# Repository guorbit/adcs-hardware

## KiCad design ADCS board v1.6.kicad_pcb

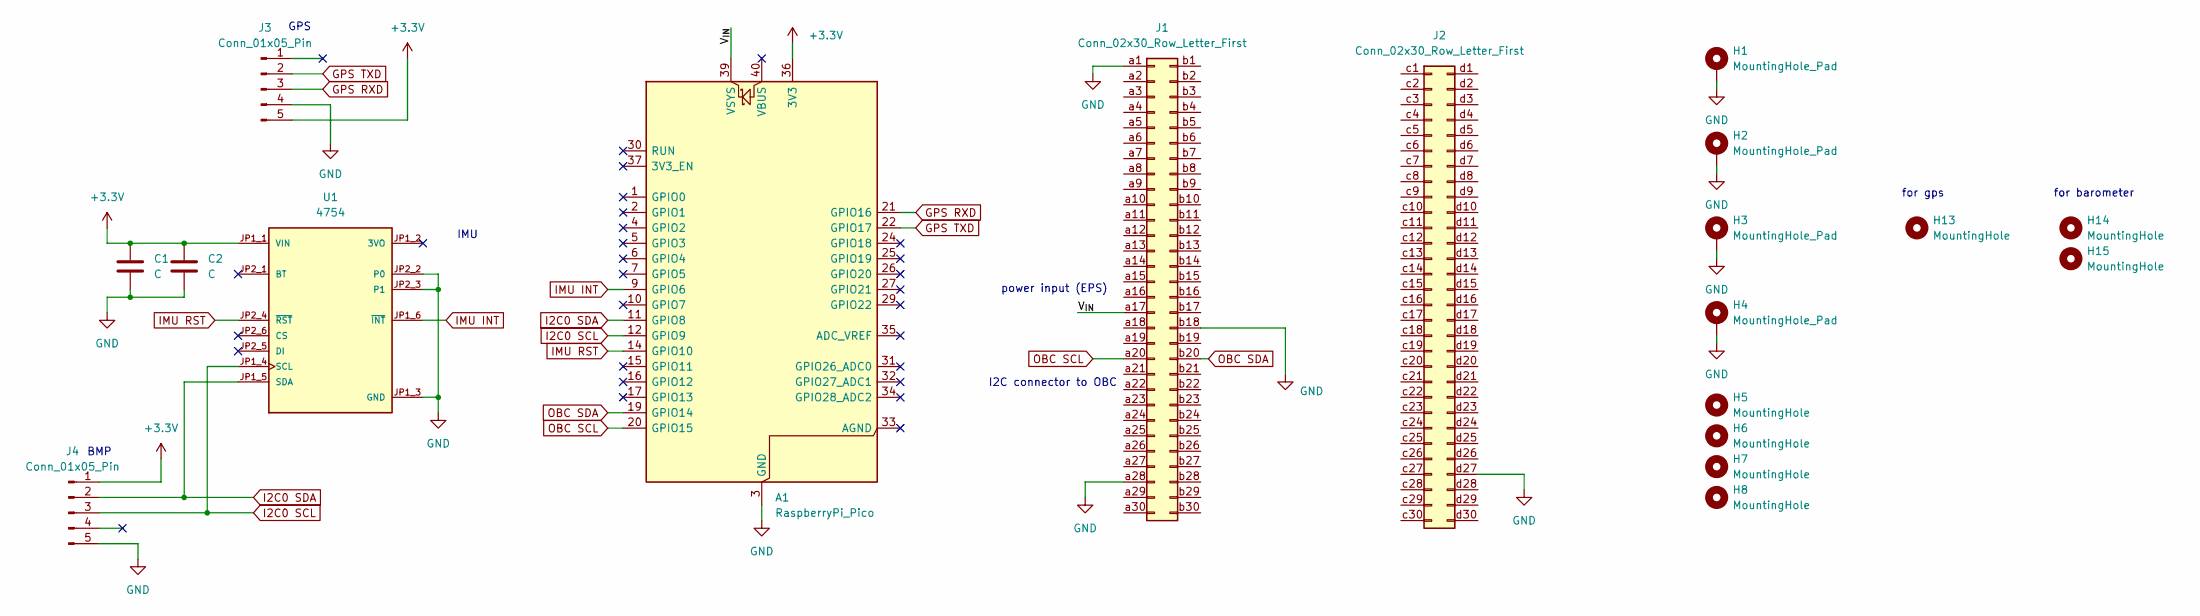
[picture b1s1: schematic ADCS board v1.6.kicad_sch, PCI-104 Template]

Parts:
A1: RaspberryPi_Pico; RaspberryPi_Pico_Common_THT
C1, C2: C; C_0603_1608Metric
H1, H2, H3, H4: MountingHole_Pad; MountingHole_3.2mm_M3_Pad_TopBottom
H5, H6, H7, H8: MountingHole; MountingHole_2mm
H13: MountingHole; MountingHole_3mm
H14, H15: MountingHole; MountingHole_2.5mm
J1, J2: Conn_02x30_Row_Letter_First; PinSocket_2x30_P2.00mm_Vertical
J3, J4: Conn_01x05_Pin; PinHeader_1x05_P2.54mm_Vertical
U1: 4754; MODULE_4754; PARTREV 2021-03-16

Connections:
+3.3V: A1.36 (3V3), C1.1, C2.1, J3.5 (VCC), J4.1 (VCC_(2-6V)), U1.JP1_1 (VIN)
/V_{IN}: A1.39 (VSYS), J1.a17
GND: A1.3 (GND), A1.8 (GND), A1.13 (GND), A1.18 (GND), A1.23 (GND), A1.28 (GND), A1.38 (GND), C1.2, C2.2, H1.1 (1_1), H2.1 (1_1), H3.1 (1_1), H4.1 (1_1), J1.a1, J1.a28, J1.b18, J2.d27 (Pin_b27_d27), J3.4 (GND), J4.5 (GND), U1.JP1_3 (GND), U1.JP2_2 (P0), U1.JP2_3 (P1)
GPS RXD: A1.21 (GPIO16), J3.3 (RXD)
GPS TXD: A1.22 (GPIO17), J3.2 (TXD)
I2C0 SCL: A1.12 (GPIO9), J4.3 (SCL), U1.JP1_4 (SCL)
I2C0 SDA: A1.11 (GPIO8), J4.2 (SDA), U1.JP1_5 (SDA)
IMU INT: A1.9 (GPIO6), U1.JP1_6 (~INT)
IMU RST: A1.14 (GPIO10), U1.JP2_4 (~RST)
OBC SCL: A1.20 (GPIO15), J1.a20
OBC SDA: A1.19 (GPIO14), J1.b20

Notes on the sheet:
for gps
power input (EPS)
BMP
GPS
I2C connector to OBC
for barometer
IMU

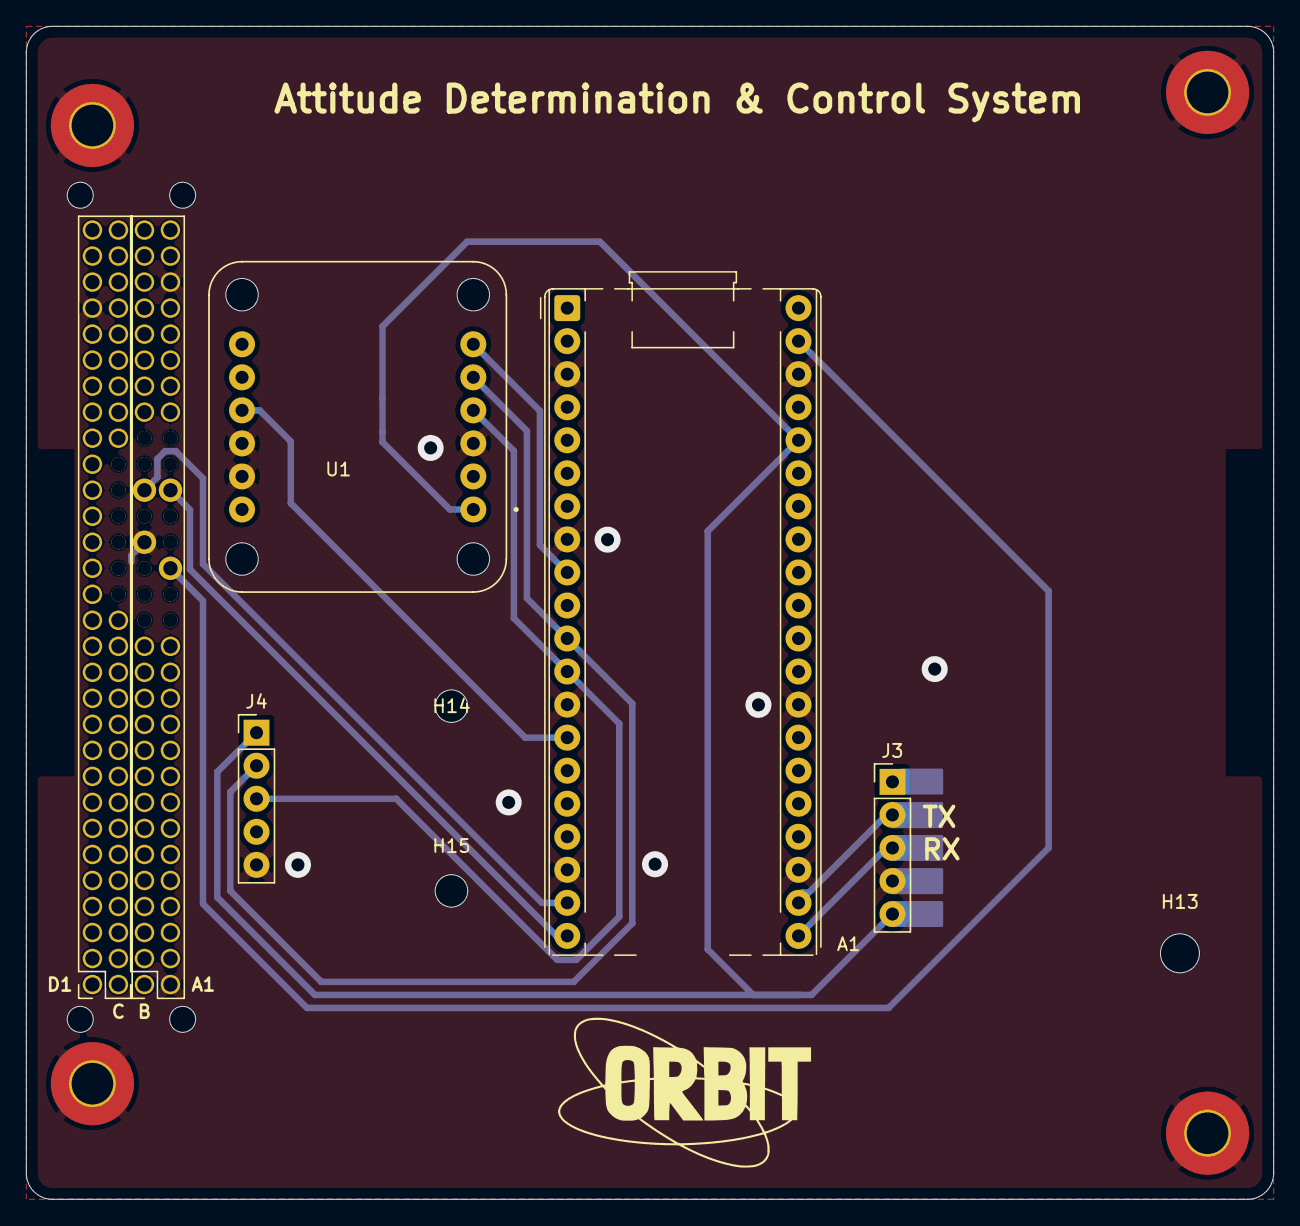
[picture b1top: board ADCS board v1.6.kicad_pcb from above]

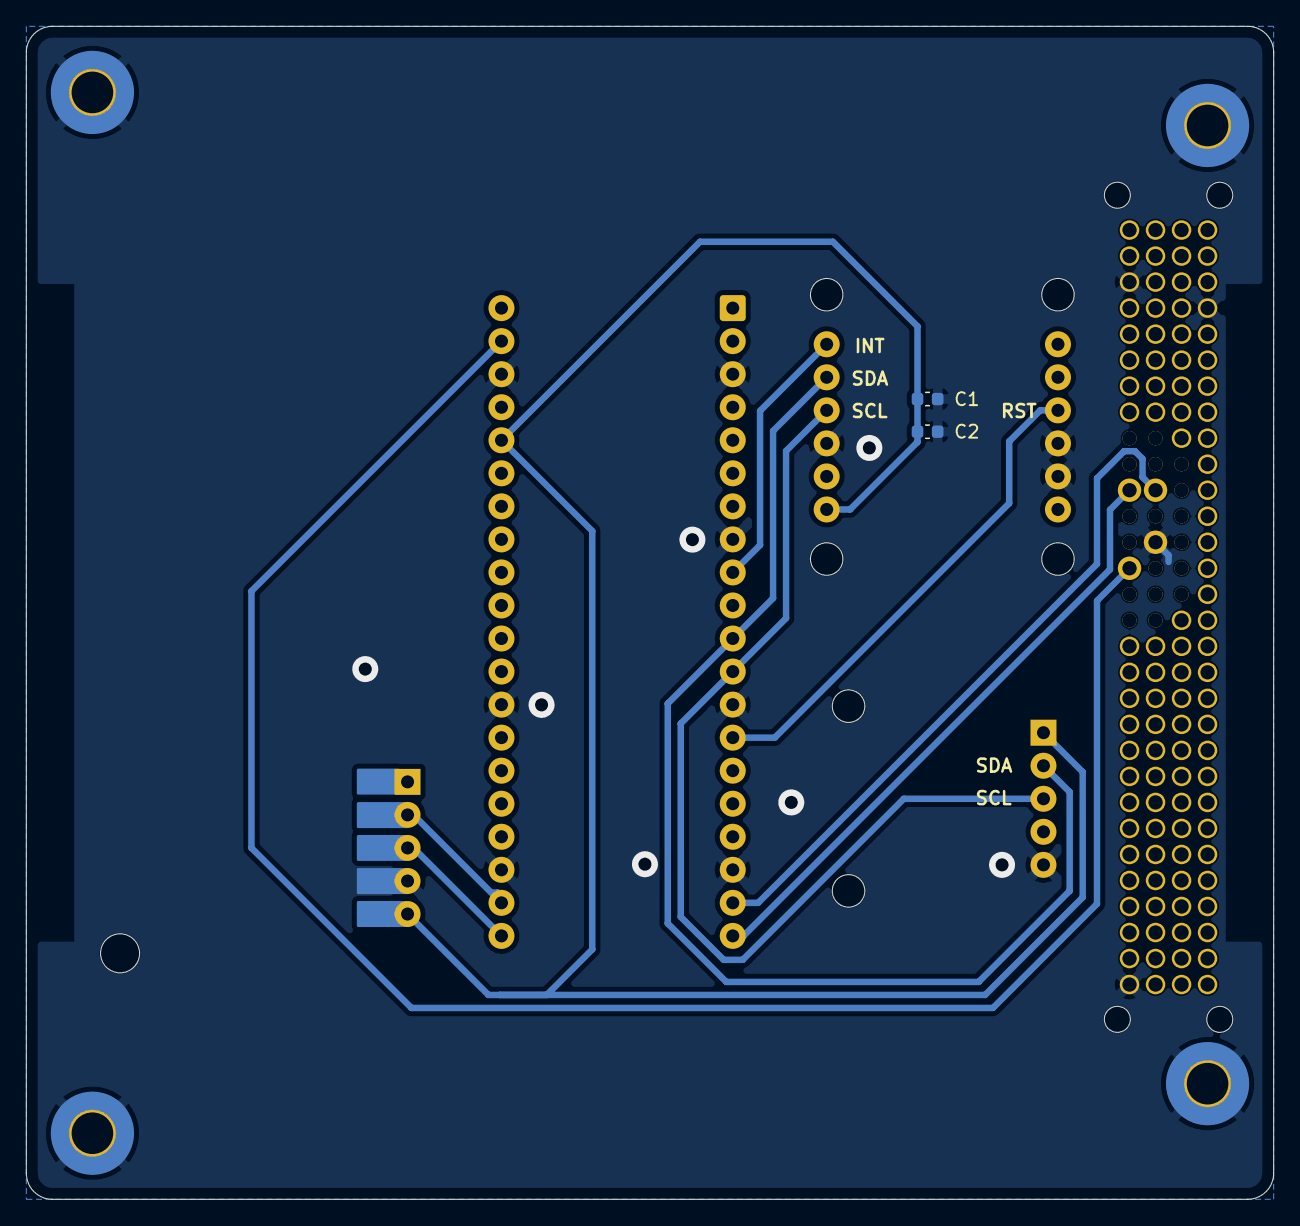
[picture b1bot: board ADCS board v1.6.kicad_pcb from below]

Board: 2 copper layers, 95.9 x 90.2 mm, 19 parts (2 on the bottom side), 11 nets.
